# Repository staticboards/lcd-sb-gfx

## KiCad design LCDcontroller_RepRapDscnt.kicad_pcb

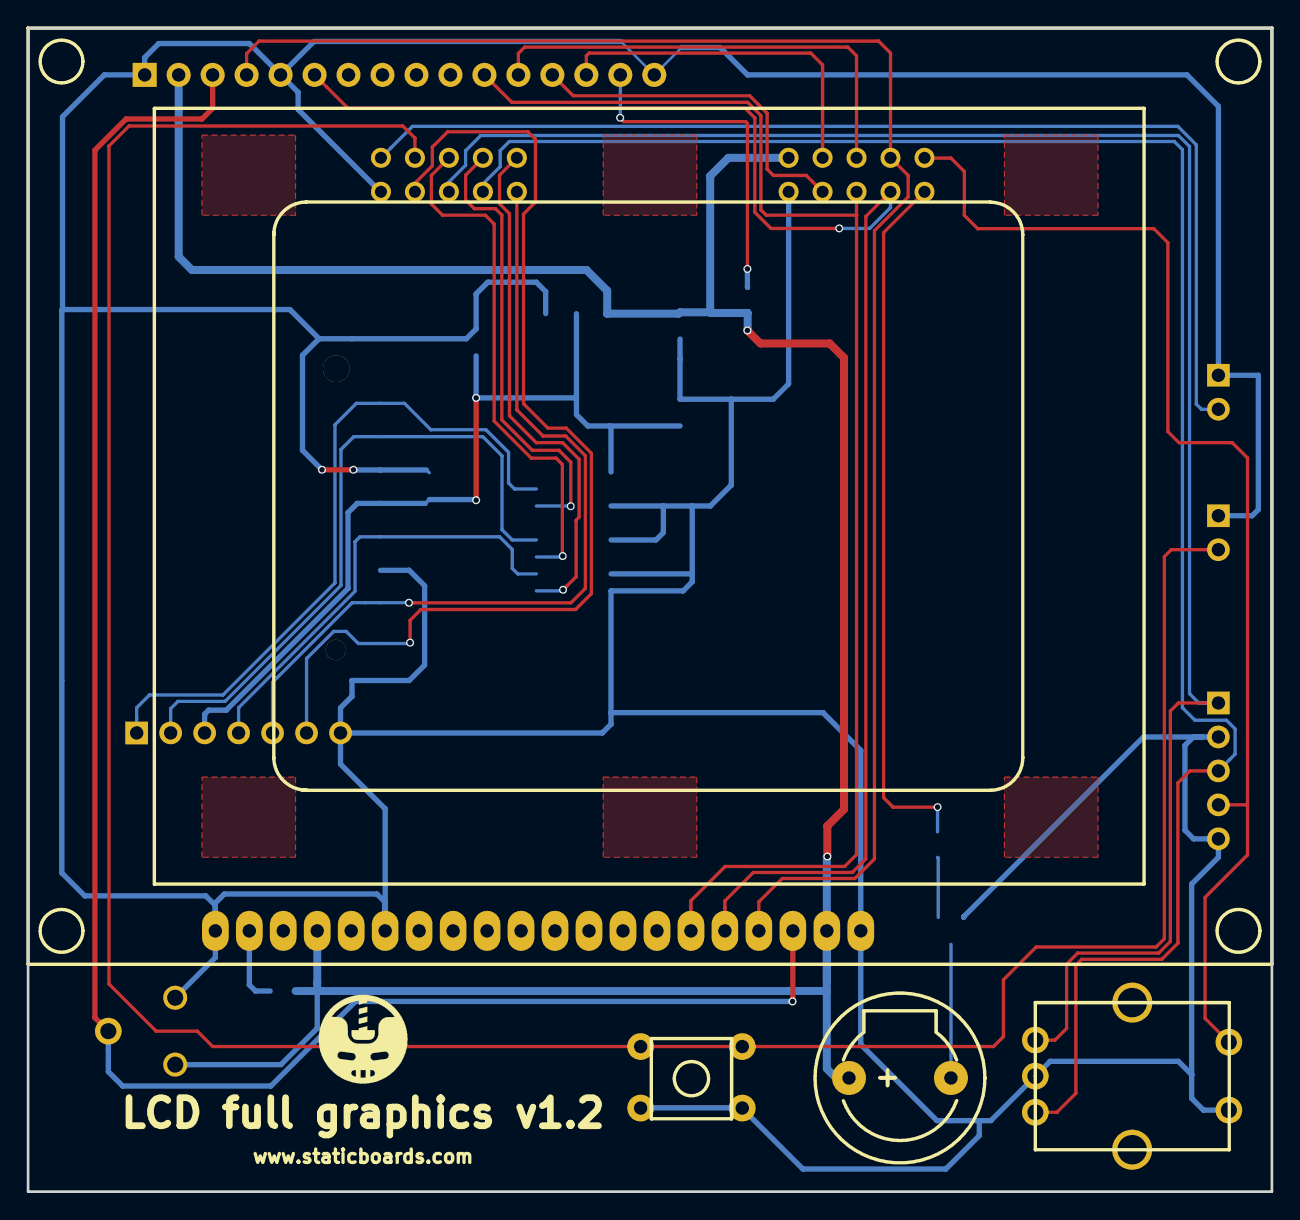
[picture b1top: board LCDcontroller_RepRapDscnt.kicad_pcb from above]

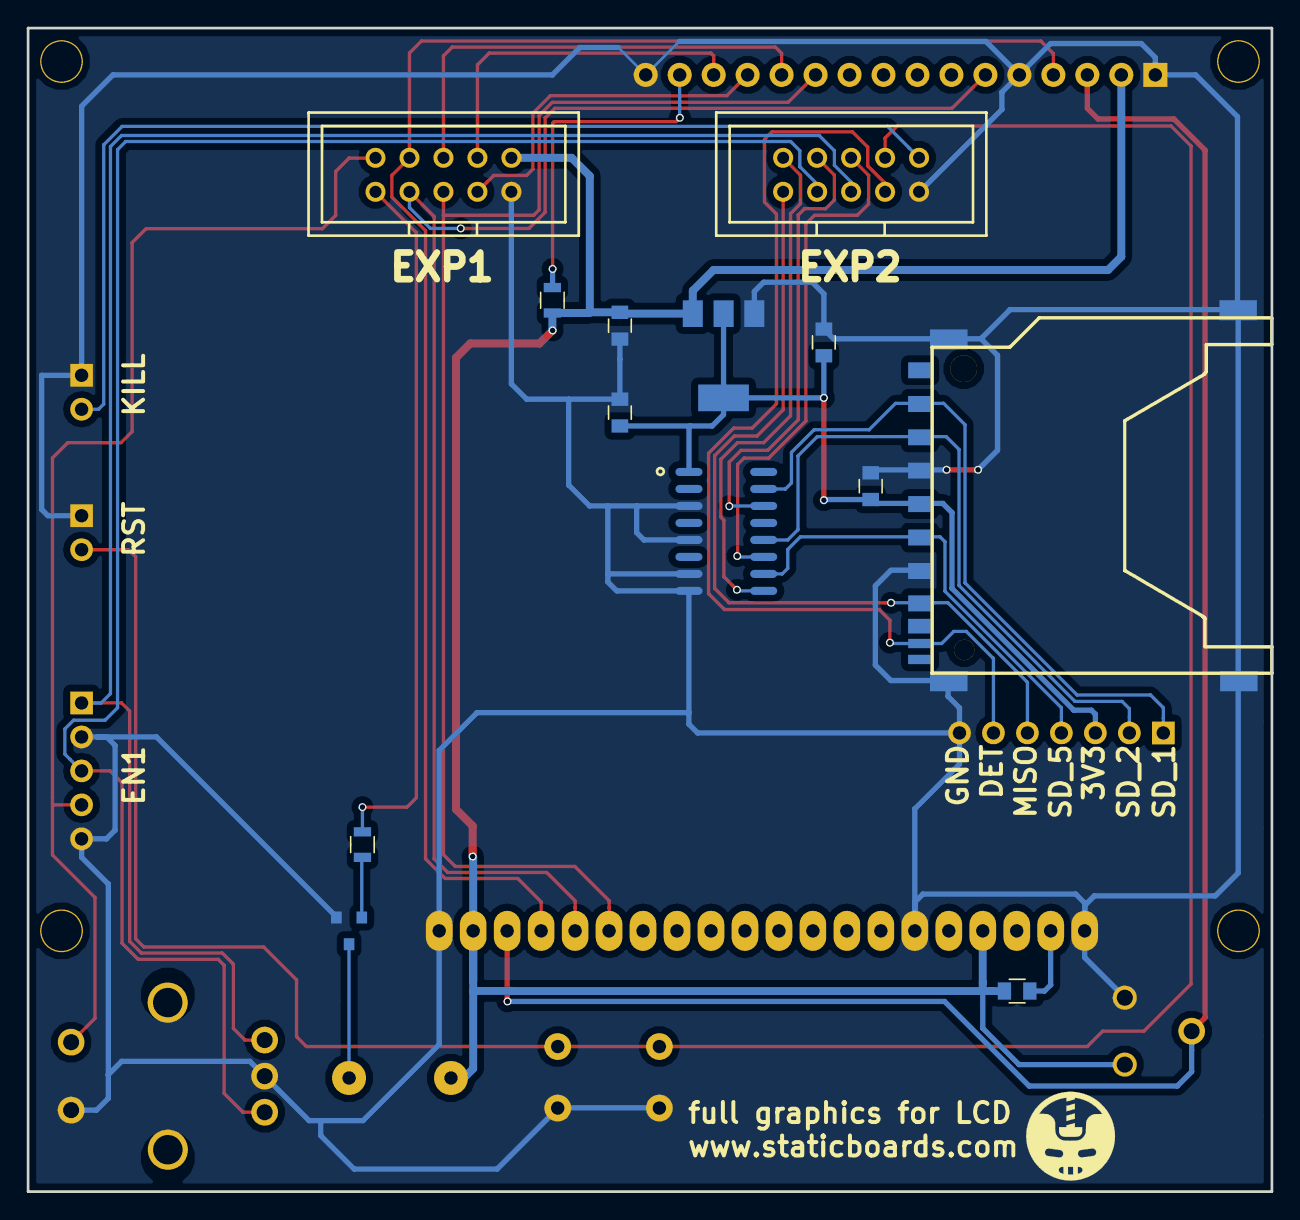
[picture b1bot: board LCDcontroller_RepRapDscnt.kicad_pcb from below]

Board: 2 copper layers, 93.0 x 87.0 mm, 23 parts (14 on the bottom side), 29 nets.

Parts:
BZ1: Buzzer; PIEZO_11mm_1
C1, C2, C3: 100nF; C_0805
C4: 1uF; C_0805
EN1: Conn_01x05; Pin_Header_Straight_1x05_Pitch2.54mm
EXP1: Conn_02x05_Odd_Even; HDR2X5_exp_1
EXP2: Conn_02x05_Odd_Even; HDR2X5_exp_2
J1: CONN_01X07; Pin_Header_Straight_1x07_Pitch2.54mm
JP1: SD_Card; SD-4_1
KILL1: Conn_01x02; Pin_Header_Straight_1x02_Pitch2.54mm
LCD12864B1: GLCD1_KXM12864M-3; KXM12864M-3_1
LCD_2004_1: Conn_01x16; SIP-16-1_1
POT_TRIM1: 10K; RES-2_1
Q1: BC817; SOT-23
R1: 1K; R_0805
RA1: 100; R_0805
RBL1: 100; R_0805
RST1: Conn_01x02; Pin_Header_Straight_1x02_Pitch2.54mm
SW1: SW_SPST; SW_6X6MM_ONE_LAYER_1
U1: LDO 3V3; SOT-223
U2: 74HC4050; SO-16_1
U4: BTN_ENC; ENCODERS_1

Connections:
+3V3: C2.1, C3.1, C4.1, J1.3, JP1.4, U1.2, U2.1
/X: LCD12864B1.7, LCD12864B1.8, LCD12864B1.9, LCD12864B1.10, LCD12864B1.11, LCD12864B1.12, LCD12864B1.13, LCD12864B1.14
BEEPER: EXP1.1, R1.2
BTN_EN1: EN1.1, EXP2.5, U4.1
BTN_EN2: EN1.3, EXP2.3, U4.3
BTN_ENC1: EN1.4, EXP1.2, U4.5
DATAIN: J1.2, JP1.2, U2.12
DATAOUT: EXP2.1, J1.5, JP1.7
GND: C1.2, C2.2, C3.2, C4.2, EN1.2, EN1.5, EXP1.9, EXP2.9, J1.7, JP1.3, JP1.6, JP1.12, JP1.13, KILL1.1, LCD12864B1.1, LCD12864B1.15, LCD12864B1.20, LCD_2004_1.1, LCD_2004_1.5, LCD_2004_1.16, POT_TRIM1.3, Q1.2, RST1.1, SW1.1, U1.1, U2.3, U2.5, U2.7, U2.8, U4.2, U4.4
INDATAIN: EXP2.6, U2.11
INSDCD: EXP2.4, U2.14
INSDCLK: EXP2.2, U2.9
KILL: EXP2.10, KILL1.2
LCD4: EXP1.5, LCD12864B1.6, LCD_2004_1.11
LCD5: EXP1.6, LCD_2004_1.12
LCD6: EXP1.7, LCD_2004_1.13
LCD7: EXP1.8, LCD_2004_1.14
LCDE: EXP1.3, LCD12864B1.5, LCD_2004_1.6
LCDRS: EXP1.4, LCD12864B1.4, LCD_2004_1.4
unnamed: BZ1.2, Q1.3
unnamed: LCD12864B1.19, RBL1.1
unnamed: LCD_2004_1.15, RA1.2
unnamed: Q1.1, R1.1
RESET: EXP2.8, RST1.2, SW1.2
SDCD: J1.1, JP1.1, U2.15
SDCLK: J1.4, JP1.5, U2.10
SDDETECT: EXP2.7, J1.6, JP1.10
VCC: BZ1.1, C1.1, EXP1.10, LCD12864B1.2, LCD12864B1.17, LCD_2004_1.2, POT_TRIM1.1, RA1.1, RBL1.2, U1.3
VO: LCD12864B1.3, LCD_2004_1.3, POT_TRIM1.2

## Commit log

2018-11-06 readme
2018-11-06 initial release
2018-11-06 creado el pdf
2018-11-06 test changes
